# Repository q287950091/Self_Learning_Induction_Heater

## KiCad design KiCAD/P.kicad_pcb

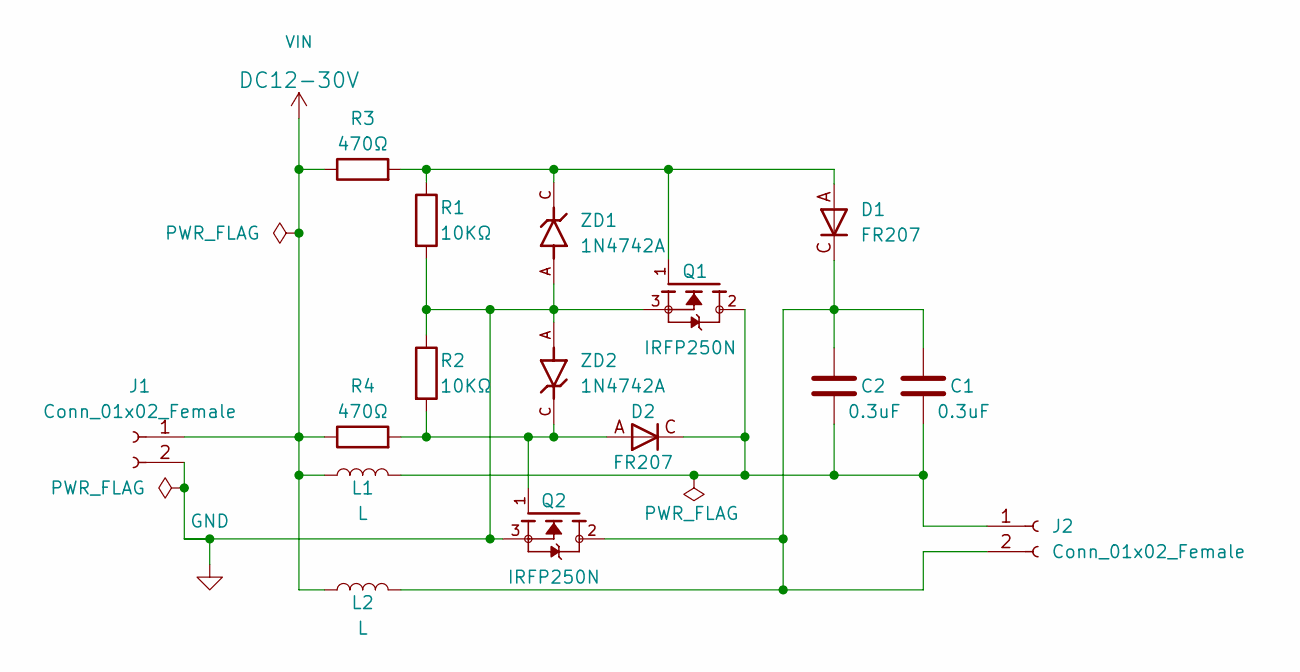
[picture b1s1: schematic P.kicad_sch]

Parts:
C1, C2: 0.3uF; MKPH_SH_0.3uF
D1, D2: FR207; DO15-12
J1, J2: Conn_01x02_Female; x2_Hub
L1, L2: L; Inductor_0.1mH
Q1, Q2: IRFP250N; TO545P1590X530X2460-3
R1, R2: 10KΩ; 1-4W_Resistor
R3, R4: 470Ω; 1W_Resistor
ZD1, ZD2: 1N4742A; DIOAD1060W70L435D230; PARTREV F1606

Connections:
GND: J1.2, Q1.3, Q2.3, R1.2, R2.1, ZD1.A, ZD2.A
unnamed: C1.1, C2.1, D1.C, J2.2, L2.2, Q2.2
unnamed: C1.2, C2.2, D2.C, J2.1, L1.2, Q1.2
unnamed: D1.A, Q1.1, R1.1, R3.2, ZD1.C
unnamed: D2.A, Q2.1, R2.2, R4.2, ZD2.C
VIN: J1.1, L1.1, L2.1, R3.1, R4.1

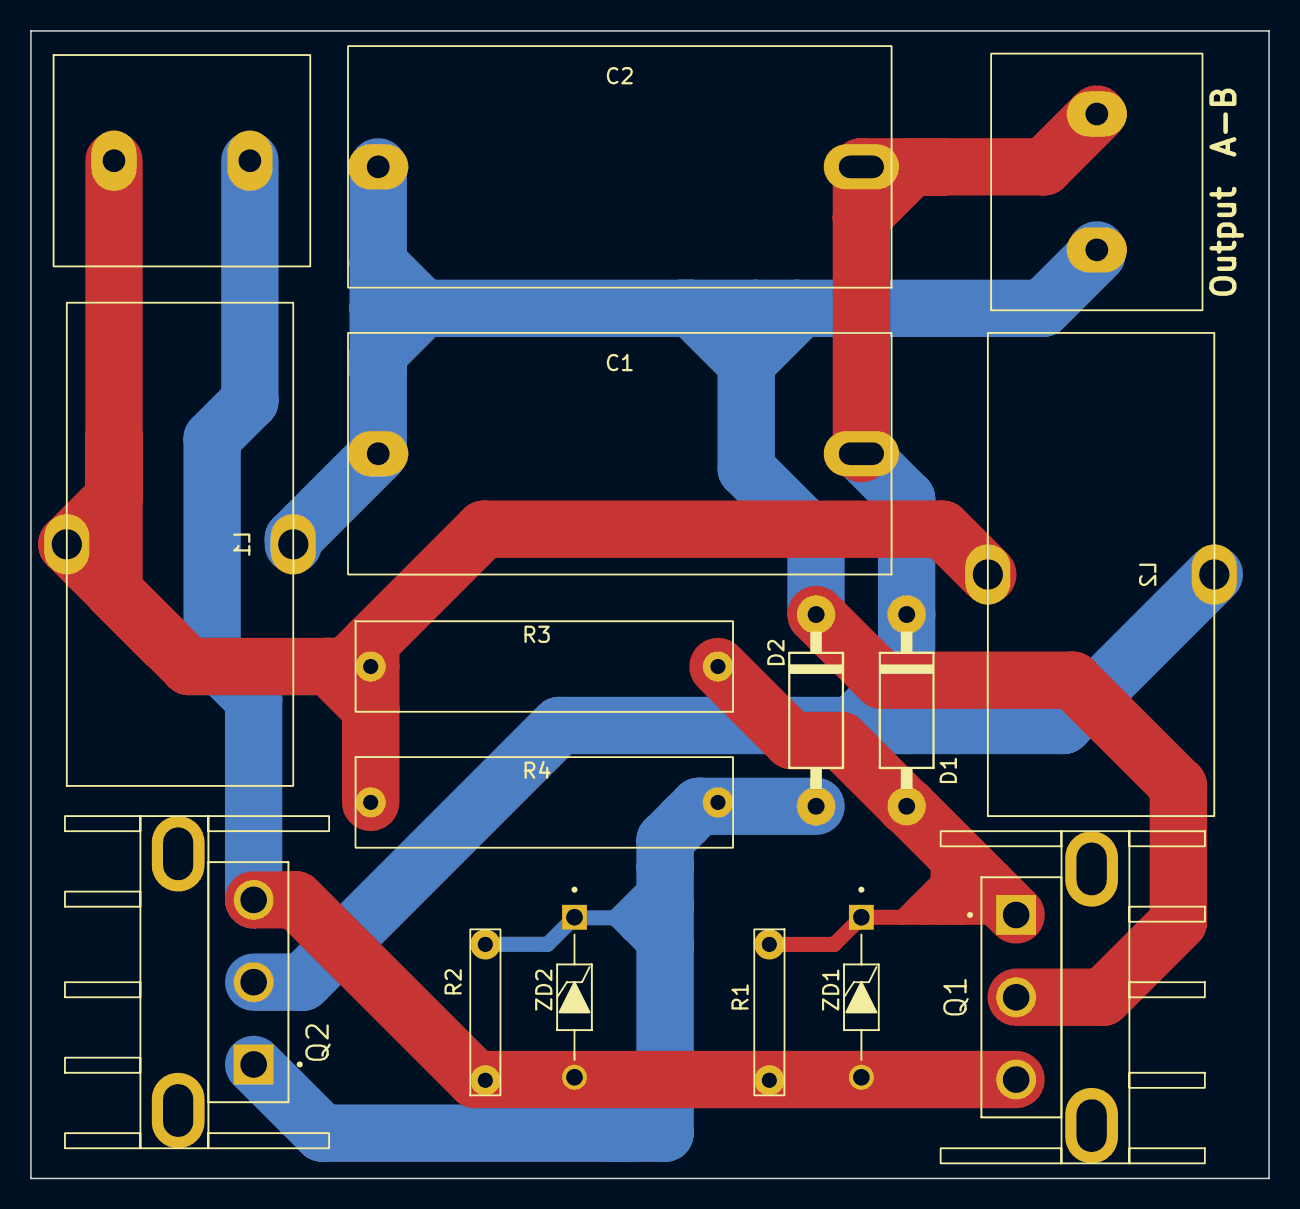
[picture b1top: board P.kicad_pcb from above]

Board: 2 copper layers, 82.0 x 76.0 mm, 16 parts (0 on the bottom side), 6 nets.
